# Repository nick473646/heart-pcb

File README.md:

The purpose of this repository is not merely to demonstrate the finished project, but to show my working progress and the steps it took along the way. 
There will be many files which are redundant or not needed if you yourself want to use this project, but I've left them as proof of my 
workflow. An example includes the DRC.rpt, which shows all of my errors on my first attempt at the layout.

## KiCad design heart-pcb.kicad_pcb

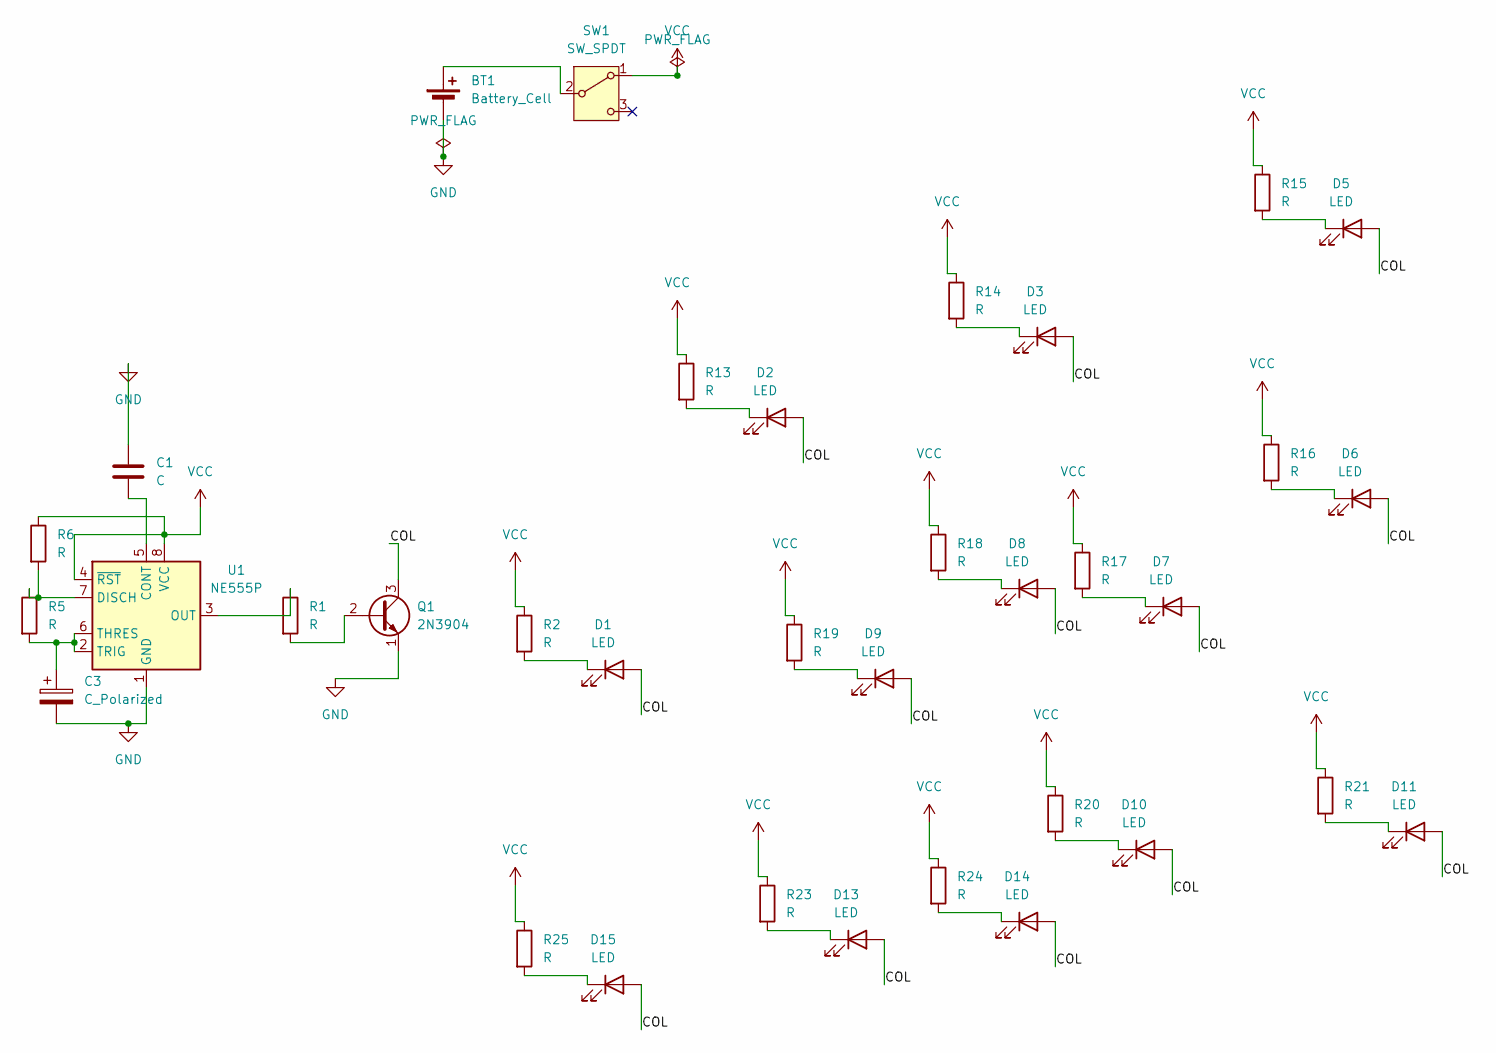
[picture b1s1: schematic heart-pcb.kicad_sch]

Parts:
BT1: Battery_Cell; BatteryHolder_Keystone_3034_1x20mm
C1: C; C_Disc_D5.0mm_W2.5mm_P5.00mm
C3: C_Polarized; CP_Radial_D5.0mm_P2.50mm
D1, D2, D3, D5, D6, D7, D8, D9, D10, D11, D13, D14, D15: LED; LED_D5.0mm
Q1: 2N3904; TO-92_Inline
R1, R2, R5, R6, R13, R14, R15, R16, R17, R18, R19, R20, R21, R23, R24, R25: R; R_Axial_DIN0207_L6.3mm_D2.5mm_P7.62mm_Horizontal
SW1: SW_SPDT; SW_Slide_SPDT_Straight_CK_OS102011MS2Q
U1: NE555P; DIP-8_W7.62mm

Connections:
/COL: D1.2 (A), D2.2 (A), D3.2 (A), D5.2 (A), D6.2 (A), D7.2 (A), D8.2 (A), D9.2 (A), D10.2 (A), D11.2 (A), D13.2 (A), D14.2 (A), D15.2 (A), Q1.3 (C)
GND: BT1.2 (-), C1.1, C3.2, Q1.1 (E), U1.1 (GND)
unnamed: BT1.1 (+), SW1.2 (B)
unnamed: D1.1 (K), R2.2
unnamed: D2.1 (K), R13.2
unnamed: D3.1 (K), R14.2
unnamed: D5.1 (K), R15.2
unnamed: D6.1 (K), R16.2
unnamed: D7.1 (K), R17.2
unnamed: D8.1 (K), R18.2
unnamed: D9.1 (K), R19.2
unnamed: D10.1 (K), R20.2
unnamed: D11.1 (K), R21.2
unnamed: D13.1 (K), R23.2
unnamed: D14.1 (K), R24.2
unnamed: D15.1 (K), R25.2
unnamed: Q1.2 (B), R1.2
unnamed: C1.2, U1.5 (CONT)
unnamed: R5.1, R6.2, U1.7 (DISCH)
unnamed: R1.1, U1.3 (OUT)
unnamed: C3.1, R5.2, U1.2 (TRIG), U1.6 (THRES)
VCC: R2.1, R6.1, R13.1, R14.1, R15.1, R16.1, R17.1, R18.1, R19.1, R20.1, R21.1, R23.1, R24.1, R25.1, SW1.1 (A), U1.4 (~RST), U1.8 (VCC)

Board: 2 copper layers, 35 parts (15 on the bottom side), 22 nets, no tracks yet.
